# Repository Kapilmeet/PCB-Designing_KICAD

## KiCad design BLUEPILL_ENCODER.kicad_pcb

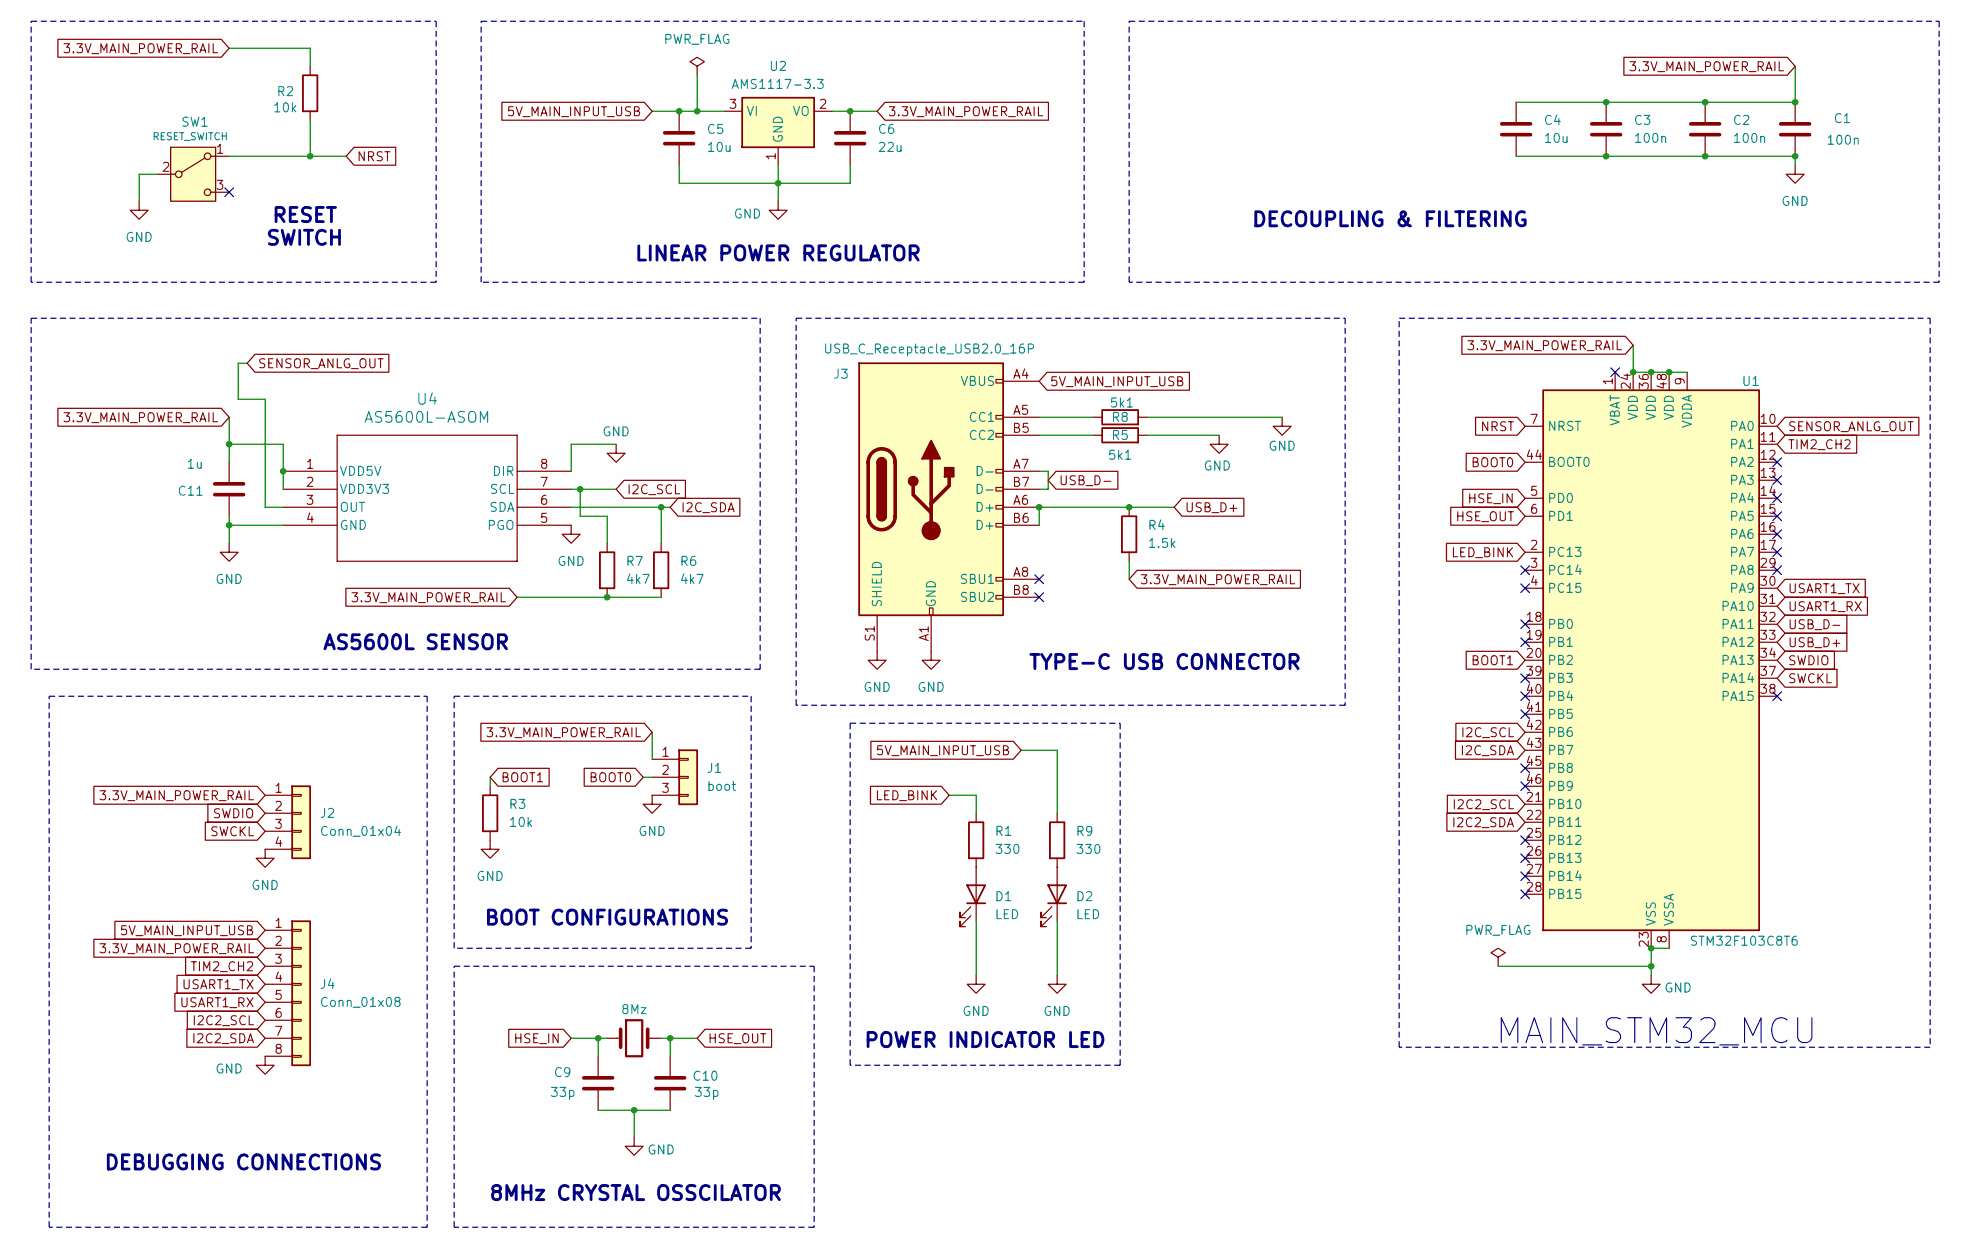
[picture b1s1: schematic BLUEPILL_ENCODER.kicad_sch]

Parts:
C1, C2, C3: 100n; C_0603_1608Metric_Pad1.08x0.95mm_HandSolder
C4, C5: 10u; C_0603_1608Metric_Pad1.08x0.95mm_HandSolder
C6: 22u; C_0603_1608Metric_Pad1.08x0.95mm_HandSolder
C9, C10: 33p; C_0603_1608Metric_Pad1.08x0.95mm_HandSolder
C11: 1u; C_0603_1608Metric_Pad1.08x0.95mm_HandSolder
D1, D2: LED; LED_0603_1608Metric_Pad1.05x0.95mm_HandSolder
J1: boot; PinHeader_1x03_P2.54mm_Vertical
J2: Conn_01x04; PinHeader_1x04_P2.54mm_Vertical
J3: USB_C_Receptacle_USB2.0_16P; USB_C_Receptacle_GCT_USB4105-xx-A_16P_TopMnt_Horizontal
J4: Conn_01x08; PinHeader_1x08_P2.54mm_Vertical
R1, R9: 330; R_0603_1608Metric_Pad0.98x0.95mm_HandSolder
R2, R3: 10k; R_0603_1608Metric_Pad0.98x0.95mm_HandSolder
R4: 1.5k; R_0603_1608Metric_Pad0.98x0.95mm_HandSolder
R5, R8: 5k1; R_0603_1608Metric_Pad0.98x0.95mm_HandSolder
R6, R7: 4k7; R_0603_1608Metric_Pad0.98x0.95mm_HandSolder
SW1: RESET_SWITCH; SW_TS09-63-25-R-260-SMT-TR
U1: STM32F103C8T6; LQFP-48_7x7mm_P0.5mm
U2: AMS1117-3.3; SOT-223-3_TabPin2
U4: AS5600L-ASOM; AS5600L-ASOM_AMS
Y2: 8Mz; XTAL_ABM3-8.000MHZ-D2Y-T

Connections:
3.3V_MAIN_POWER_RAIL: C1.1, C2.1, C3.1, C4.1, C6.1, C11.2, J1.1, J2.1, J4.2, R2.1, R4.2, R6.2, R7.2, U1.9 (VDDA), U1.24 (VDD), U1.36 (VDD), U1.48 (VDD), U2.2 (VO), U4.1 (VDD5V), U4.2 (VDD3V3)
5V_MAIN_INPUT_USB: C5.1, J3.A4 (VBUS), J3.A9 (VBUS), J3.B4 (VBUS), J3.B9 (VBUS), J4.1, R9.1, U2.3 (VI)
BOOT0: J1.2, U1.44 (BOOT0)
BOOT1: R3.1, U1.20 (PB2)
GND: C1.2, C2.2, C3.2, C4.2, C5.2, C6.2, C9.2, C10.2, C11.1, D1.1 (K), D2.1 (K), J1.3, J2.4, J3.A1 (GND), J3.A12 (GND), J3.B1 (GND), J3.B12 (GND), J3.S1 (SHIELD), J4.8, R3.2, R5.2, R8.2, SW1.2 (B), U1.8 (VSSA), U1.23 (VSS), U1.35 (VSS), U1.47 (VSS), U2.1 (GND), U4.4 (GND), U4.5 (PGO), U4.8 (DIR)
HSE_IN: C9.1, U1.5 (PD0), Y2.1
HSE_OUT: C10.1, U1.6 (PD1), Y2.2
I2C2_SCL: J4.6, U1.21 (PB10)
I2C2_SDA: J4.7, U1.22 (PB11)
I2C_SCL: R7.1, U1.42 (PB6), U4.7 (SCL)
I2C_SDA: R6.1, U1.43 (PB7), U4.6 (SDA)
LED_BINK: R1.1, U1.2 (PC13)
NRST: R2.2, SW1.1 (A), U1.7 (NRST)
unnamed: D1.2 (A), R1.2
unnamed: D2.2 (A), R9.2
unnamed: J3.A5 (CC1), R8.1
unnamed: J3.B5 (CC2), R5.1
SENSOR_ANLG_OUT: U1.10 (PA0), U4.3 (OUT)
SWCKL: J2.3, U1.37 (PA14)
SWDIO: J2.2, U1.34 (PA13)
TIM2_CH2: J4.3, U1.11 (PA1)
USART1_RX: J4.5, U1.31 (PA10)
USART1_TX: J4.4, U1.30 (PA9)
USB_D+: J3.A6 (D+), J3.B6 (D+), R4.1, U1.33 (PA12)
USB_D-: J3.A7 (D-), J3.B7 (D-), U1.32 (PA11)

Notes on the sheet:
RESET SWITCH
8MHz CRYSTAL OSSCILATOR
DECOUPLING & FILTERING
POWER INDICATOR LED
DEBUGGING CONNECTIONS
MAIN_STM32_MCU
LINEAR POWER REGULATOR
AS5600L SENSOR
TYPE-C USB CONNECTOR
BOOT CONFIGURATIONS

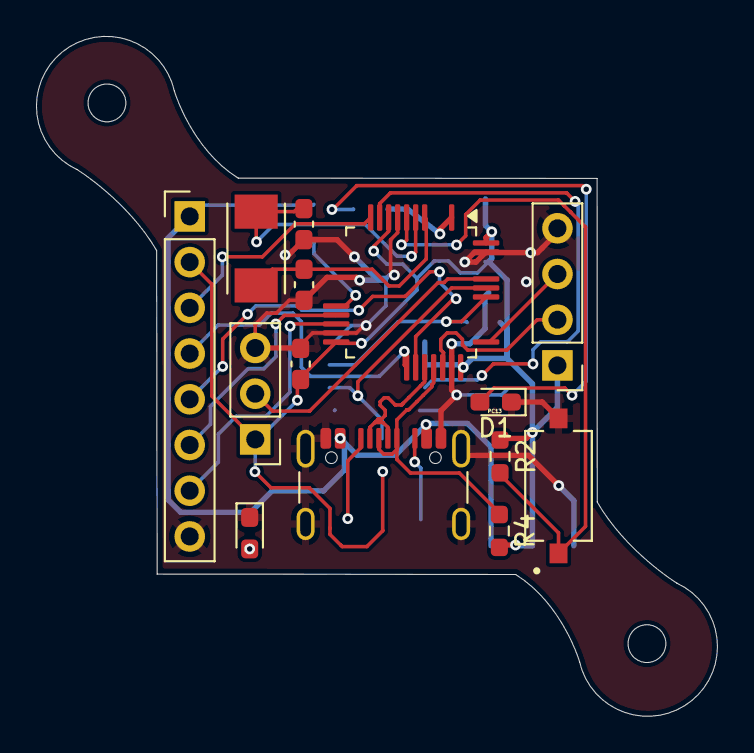
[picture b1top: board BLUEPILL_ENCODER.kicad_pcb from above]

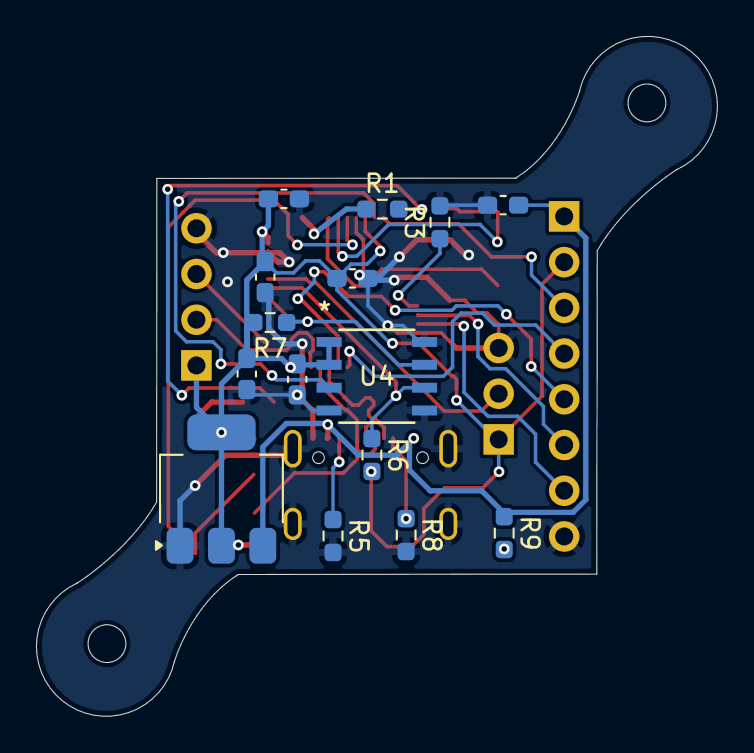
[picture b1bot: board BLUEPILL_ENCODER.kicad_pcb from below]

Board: 2 copper layers, 37.8 x 37.8 mm, 29 parts (15 on the bottom side), 25 nets.

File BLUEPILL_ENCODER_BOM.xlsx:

bomfinal
Reference | Product | Footprint | Value / Part | Authorerised Vendor buy link | Price of unit | Quantity | Amount (Rs) | Vendor | SKU Number
C1,C2,C3 | 100nf | Capacitor_SMD:C_0603_1608Metric_Pad1.08x0.95mm_HandSolder | 100nF 0603 Surface Mount Multilayer Ceramic Capacitor | https://robu.in/product/100nf-0603-surface-mount-multilayer-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 | 0.36 | 3 | 1.08 | Robu | 594998
C4,C5 | 10uf | Capacitor_SMD:C_0603_1608Metric_Pad1.08x0.95mm_HandSolder | GRM188R61E106KA73J-MURATA 10 µF, 25 V, 0603 | https://robu.in/product/grm188r61e106ka73j-murata-smd-multil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 | 9 | 2 | 18 | Robu | R109079
C6 | 22uf | Capacitor_SMD:C_0603_1608Metric_Pad1.08x0.95mm_HandSolder | 22uF 0603 X5R Capacitor | https://evelta.com/22uf-10v-20-x5r-0603-capacitor/ | 5.5 | 1 | 5.5 | Evelta | 110-CL10A226MP8NUNE
C9,C10 | 33pf | Capacitor_SMD:C_0603_1608Metric_Pad1.08x0.95mm_HandSolder | 33pF 50V Ceramic Capacitor | https://sharvielectronics.com/product/33pf-50v-ceramic-capacitor/ | 0.68 | 2 | 1.36 | Sharvi | ST2001CO0471
C11 | 1uf | Capacitor_SMD:C_0603_1608Metric_Pad1.08x0.95mm_HandSolder | 1uF 0603 Surface Mount Ceramic Capacitor | https://robu.in/product/cl10a105ko8nnwc-samsang-16v-1uf-x5r-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 | 0.36 | 1 | 0.36 | Robu | R172314
D1,D2 | Red smd LEDs | LED_SMD:LED_0603_1608Metric_Pad1.05x0.95mm_HandSolder | SMD LED 0603 (Red/Green) | https://robu.in/product/xl-1608vrc-06-xinglight-5ma-90mcd-re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 | 1.4 | 2 | 2.8 | Robu | R199109
J1 | HeaderPin_01x03 | Connector_PinHeader_2.54mm:PinHeader_1x03_P2.54mm_Vertical | 3-Pin Male Header 2.54mm | https://robu.in/product/1x40-berg-strip-male-connector/ | - | 1 | - | Robu | 470829
J2 | HeaderPin_01x04 | Connector_PinHeader_2.54mm:PinHeader_1x04_P2.54mm_Vertical | 4-Pin Male Header 2.54mm | https://robu.in/product/1x40-berg-strip-male-connector/ | - | 1 | - | Robu | 470829
J3 | USB_C_Receptacle_USB2.0_16P | Connector_USB:USB_C_Receptacle_GCT_USB4105-xx-A_16P_TopMnt_Horizontal | 16 Pin C Type USB Connector - SMD Package | https://sharvielectronics.com/product/16-pin-c-type-usb-conn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 | 17.45 | 1 | 17.45 | Sharvi | ST2103SD0931
J4 | HeaderPin_01x08 | Connector_PinHeader_2.54mm:PinHeader_1x08_P2.54mm_Vertical | 8-Pin Male Header 2.54mm | https://robu.in/product/1x40-berg-strip-male-connector/ | 8 | 1 | 8 | Robu | 470829
R1,R9 | 330Ω | Resistor_SMD:R_0603_1608Metric_Pad0.98x0.95mm_HandSolder | 330 Ohm 1/4W 0603 Chip Resistor | https://sharvielectronics.com/product/330-ohm-1-10-watt-resi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 | 0.75 | 2 | 1.5 | Sharvi | ST2009SD0412
R2,R3 | 10k | Resistor_SMD:R_0603_1608Metric_Pad0.98x0.95mm_HandSolder | 10k Ohm 1/4W 0603 SMDResistor | https://sharvielectronics.com/product/10k-ohm-1-10-watt-smd-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 | 0.85 | 2 | 2.25 | Sharvi | ST2009SD0393
R4 | 1.5k | Resistor_SMD:R_0603_1608Metric_Pad0.98x0.95mm_HandSolder | 1.5k Ohm 1/4W 0603 SMD Resistor | https://sharvielectronics.com/product/1-5k-ohm-1-10-watt-res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 | 0.95 | 1 | 0.95 | Sharvi | ST2009SD0389
R5,R8 | 5k1 | Resistor_SMD:R_0603_1608Metric_Pad0.98x0.95mm_HandSolder | 5.1k Ohm 1/4W 0603 SMD Resistor | https://sharvielectronics.com/product/5-1k-ohm-1-10-watt-res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 | 0.85 | 2 | 2.25 | Sharvi | ST2009SD0557
R6,R7 | 4k7 | Resistor_SMD:R_0603_1608Metric_Pad0.98x0.95mm_HandSolder | 4.7k Ohm 1/4W 0603 SMD Resistor | https://sharvielectronics.com/product/4-7k-ohm-1-10-watt-res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 | 0.85 | 2 | 1.7 | Sharvi | ST2009SD0415
SW1 | RESET_SWITCH | TS09-stm32_reset_original_button:SW_TS09-63-25-R-260-SMT-TR | 2Pin SMD Tactile Switch | https://sharvielectronics.com/product/3x6x2-5mm-2pin-smd-tac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 | 6.54 | 1 | 6.54 | Sharvi | ST2009SD0587
U1 | STM32F103C8T6 | Package_QFP:LQFP-48_7x7mm_P0.5mm | STM32F103C8T6 ARM Microcontroller LQFP-48 | https://sharvielectronics.com/product/stm32f103c8t6-arm-micr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 | 118.75 | 1 | 118.75 | Sharvi | ST2103SD0969
U2 | AMS1117-3.3V | Package_TO_SOT_SMD:SOT-223-3_TabPin2 | AMS1117-3.3V, 1A, SOT-223 Voltage Regulator IC | https://robu.in/product/ams1117-3-3v-1a-sot-223-voltage-regu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 | 9 | 1 | 9 | Robu | 162032
U4 | AS5600L-ASOM | ul_AS5600L-ASOM:AS5600L-ASOM_AMS | Magnetic encoder sensor module AS5600 | https://robu.in/product/as5600-asom-ams-0360-soic-8-position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 | 166 | 1 | 166 | Robu | R182262
Y2 | 8Mz CRYSTAL | ABM3-8.000MHZ-D2Y-T__ABRACON_8MHz_crystral:XTAL_ABM3-8.000MHZ-D2Y-T | YSX530GA 8MHZ 20PF 10PPM 2Pad SMD/SMT Crystal | https://evelta.com/ysx530ga-8mhz-20pf-10ppm-2pad-smd-smt-crystal/ | 48.32 | 1 | 48.32 | Evelta | YSX530GA

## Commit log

2026-02-18 Add files via upload
    Pcb is ready, free from critical errors
    Ready for manufacturing
2026-02-20 Add files via upload
    SIGNIFICANTLY REDUCED TRACE LENGTH OF I2C PULL-UPs
    AND ERRORS RECTIFIED
2026-02-20 Add files via upload
    Bill of materials file
2026-02-20 Add files via upload
    ADJUSTMENTS DONE IN SOME VIAs near the STM32 chip
